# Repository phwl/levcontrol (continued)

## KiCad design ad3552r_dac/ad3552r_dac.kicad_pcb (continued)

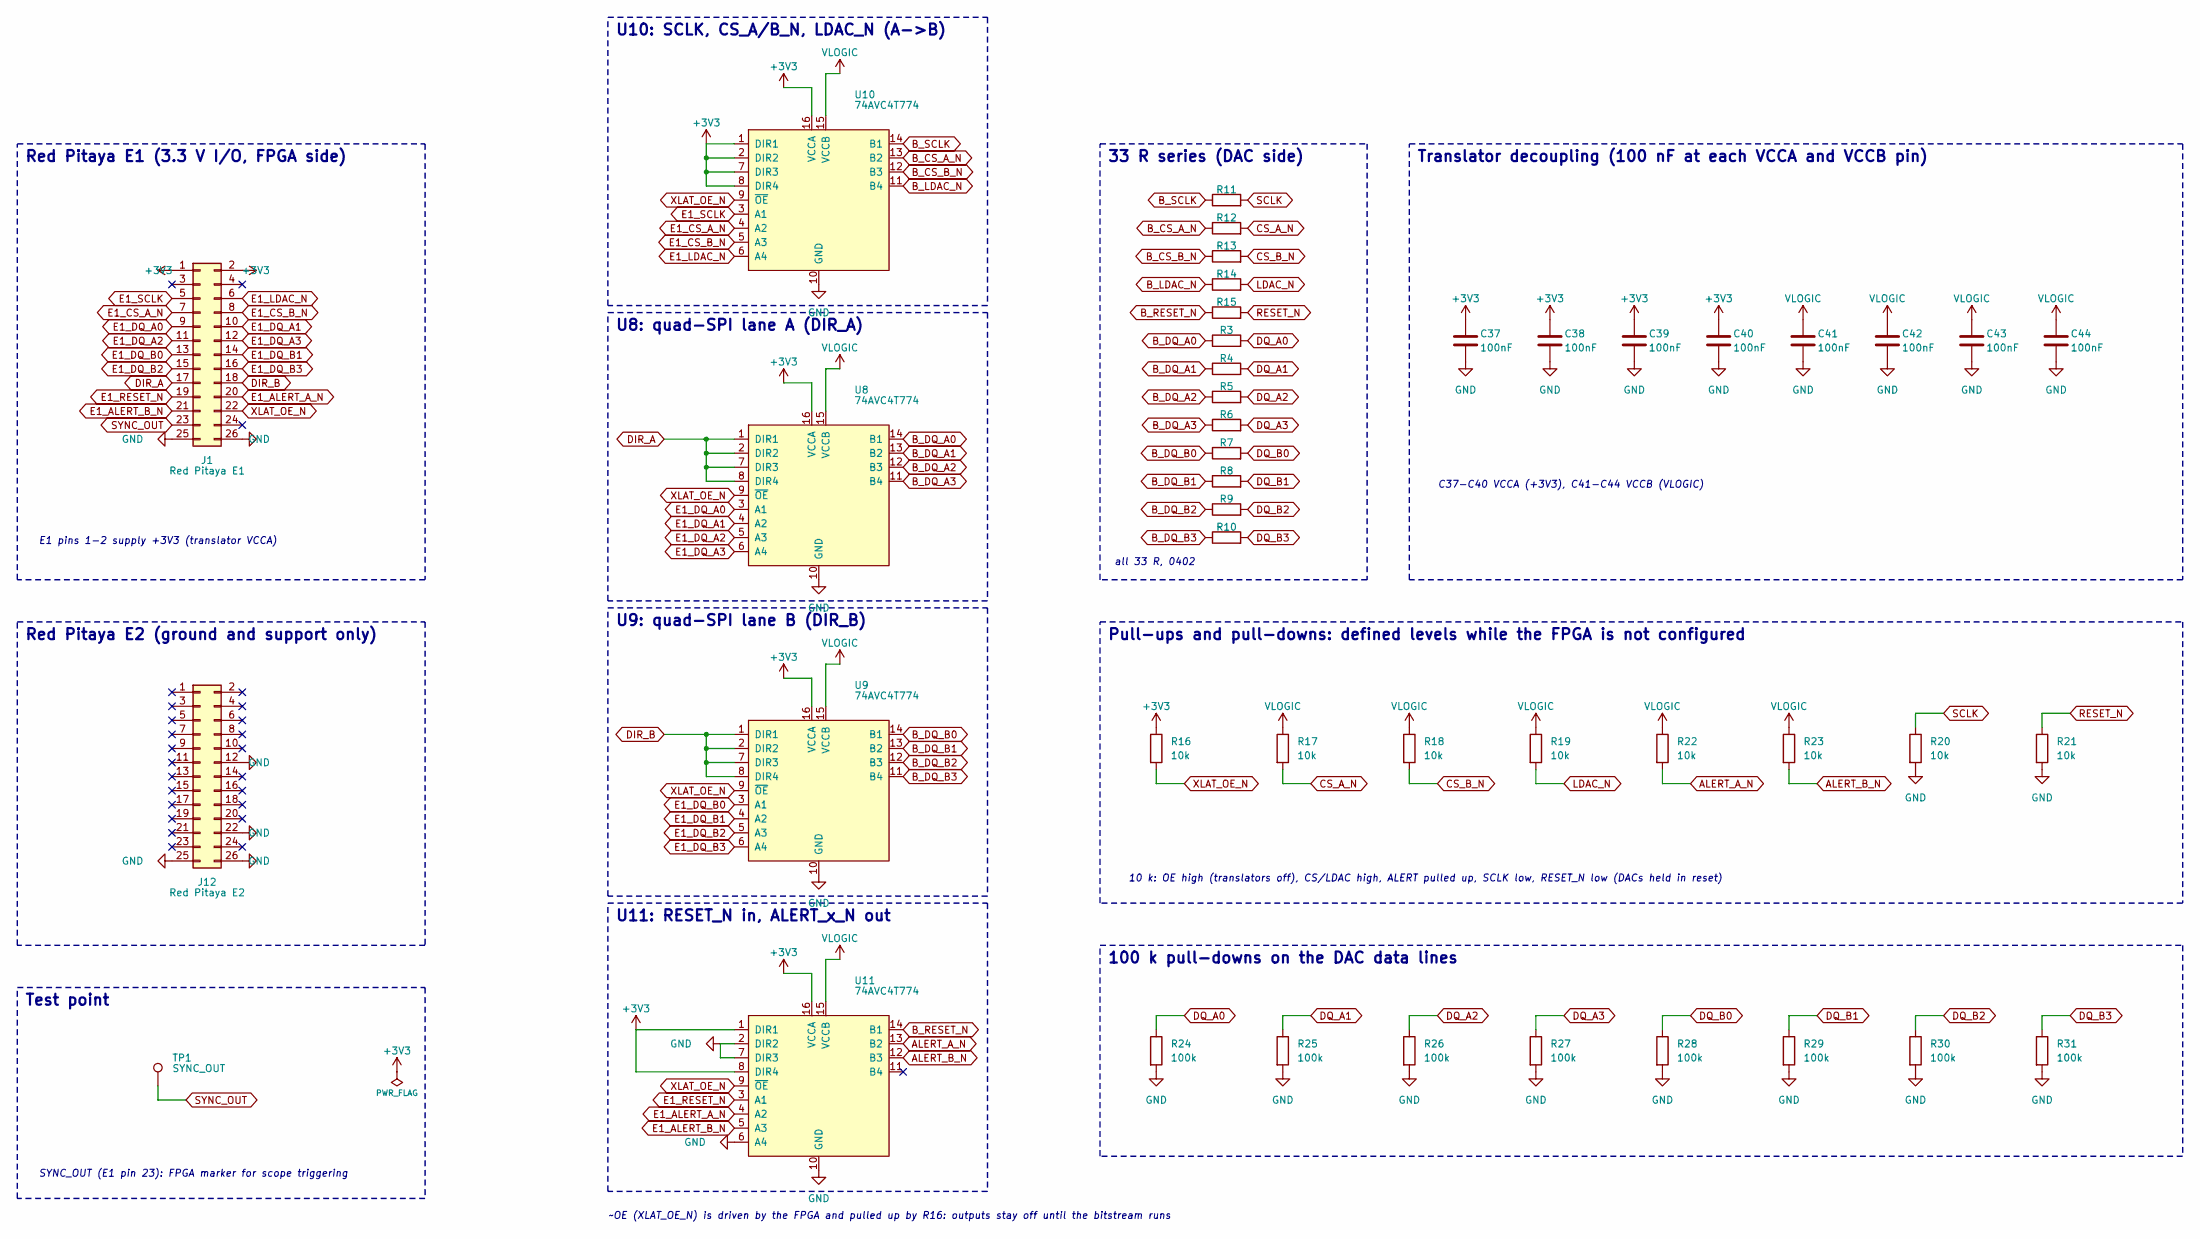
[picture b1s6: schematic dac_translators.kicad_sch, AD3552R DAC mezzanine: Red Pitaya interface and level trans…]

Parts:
C37, C38, C39, C40, C41, C42, C43, C44: 100nF; C_0402_1005Metric; MPN CL05B104KO5NNNC; LCSC C1525
J1: Red Pitaya E1; PinSocket_2x13_P2.54mm_Vertical; MPN ESW-113-33-T-D; LCSC C7498573
J12: Red Pitaya E2; PinSocket_2x13_P2.54mm_Vertical; MPN ESW-113-33-T-D; LCSC C7498573
R3, R4, R5, R6, R7, R8, R9, R10, R11, R12, R13, R14, R15: 33; R_0402_1005Metric; MPN 0402WGF330JTCE; LCSC C25105
R16, R17, R18, R19, R20, R21, R22, R23: 10k; R_0402_1005Metric; MPN 0402WGF1002TCE; LCSC C25744
R24, R25, R26, R27, R28, R29, R30, R31: 100k; R_0402_1005Metric; MPN 0402WGF1003TCE; LCSC C25741
TP1: SYNC_OUT; TestPoint_Pad_D1.5mm
U8, U9, U10, U11: 74AVC4T774; TSSOP-16_4.4x5mm_P0.65mm; MPN 74AVC4T774PWJ; LCSC C546276

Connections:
+3V3: C37.1, C38.1, C39.1, C40.1, J1.1, J1.2, R16.1, U8.16 (VCCA), U9.16 (VCCA), U10.1 (DIR1), U10.2 (DIR2), U10.7 (DIR3), U10.8 (DIR4), U10.16 (VCCA), U11.1 (DIR1), U11.8 (DIR4), U11.16 (VCCA)
ALERT_A_N: R22.2, U11.13 (B2); also elsewhere on the board
ALERT_B_N: R23.2, U11.12 (B3); also elsewhere on the board
B_CS_A_N: R12.1, U10.13 (B2)
B_CS_B_N: R13.1, U10.12 (B3)
B_DQ_A0: R3.1, U8.14 (B1)
B_DQ_A1: R4.1, U8.13 (B2)
B_DQ_A2: R5.1, U8.12 (B3)
B_DQ_A3: R6.1, U8.11 (B4)
B_DQ_B0: R7.1, U9.14 (B1)
B_DQ_B1: R8.1, U9.13 (B2)
B_DQ_B2: R9.1, U9.12 (B3)
B_DQ_B3: R10.1, U9.11 (B4)
B_LDAC_N: R14.1, U10.11 (B4)
B_RESET_N: R15.1, U11.14 (B1)
B_SCLK: R11.1, U10.14 (B1)
CS_A_N: R12.2, R17.2; also elsewhere on the board
CS_B_N: R13.2, R18.2; also elsewhere on the board
DIR_A: J1.17, U8.1 (DIR1), U8.2 (DIR2), U8.7 (DIR3), U8.8 (DIR4)
DIR_B: J1.18, U9.1 (DIR1), U9.2 (DIR2), U9.7 (DIR3), U9.8 (DIR4)
DQ_A0: R3.2, R24.1; also elsewhere on the board
DQ_A1: R4.2, R25.1; also elsewhere on the board
DQ_A2: R5.2, R26.1; also elsewhere on the board
DQ_A3: R6.2, R27.1; also elsewhere on the board
DQ_B0: R7.2, R28.1; also elsewhere on the board
DQ_B1: R8.2, R29.1; also elsewhere on the board
DQ_B2: R9.2, R30.1; also elsewhere on the board
DQ_B3: R10.2, R31.1; also elsewhere on the board
E1_ALERT_A_N: J1.20, U11.4 (A2)
E1_ALERT_B_N: J1.21, U11.5 (A3)
E1_CS_A_N: J1.7, U10.4 (A2)
E1_CS_B_N: J1.8, U10.5 (A3)
E1_DQ_A0: J1.9, U8.3 (A1)
E1_DQ_A1: J1.10, U8.4 (A2)
E1_DQ_A2: J1.11, U8.5 (A3)
E1_DQ_A3: J1.12, U8.6 (A4)
E1_DQ_B0: J1.13, U9.3 (A1)
E1_DQ_B1: J1.14, U9.4 (A2)
E1_DQ_B2: J1.15, U9.5 (A3)
E1_DQ_B3: J1.16, U9.6 (A4)
E1_LDAC_N: J1.6, U10.6 (A4)
E1_RESET_N: J1.19, U11.3 (A1)
E1_SCLK: J1.5, U10.3 (A1)
GND: C37.2, C38.2, C39.2, C40.2, C41.2, C42.2, C43.2, C44.2, J1.25, J1.26, J12.12, J12.22, J12.25, J12.26, R20.2, R21.2, R24.2, R25.2, R26.2, R27.2, R28.2, R29.2, R30.2, R31.2, U8.10 (GND), U9.10 (GND), U10.10 (GND), U11.2 (DIR2), U11.6 (A4), U11.7 (DIR3), U11.10 (GND); also elsewhere on the board
LDAC_N: R14.2, R19.2; also elsewhere on the board
RESET_N: R15.2, R21.1; also elsewhere on the board
SCLK: R11.2, R20.1; also elsewhere on the board
SYNC_OUT: J1.23, TP1.1
VLOGIC: C41.1, C42.1, C43.1, C44.1, R17.1, R18.1, R19.1, R22.1, R23.1, U8.15 (VCCB), U9.15 (VCCB), U10.15 (VCCB), U11.15 (VCCB); also elsewhere on the board
XLAT_OE_N: J1.22, R16.2, U8.9 (~OE), U9.9 (~OE), U10.9 (~OE), U11.9 (~OE)

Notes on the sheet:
U10: SCLK, CS_A/B_N, LDAC_N (A->B)
U8: quad-SPI lane A (DIR_A)
all 33 R, 0402
~OE (XLAT_OE_N) is driven by the FPGA and pulled up by R16: outputs stay off until the bitstream runs
Pull-ups and pull-downs: defined levels while the FPGA is not configured
E1 pins 1-2 supply +3V3 (translator VCCA)
100 k pull-downs on the DAC data lines
10 k: OE high (translators off), CS/LDAC high, ALERT pulled up, SCLK low, RESET_N low (DACs held in reset)
C37-C40 VCCA (+3V3), C41-C44 VCCB (VLOGIC)
Translator decoupling (100 nF at each VCCA and VCCB pin)
Red Pitaya E1 (3.3 V I/O, FPGA side)
Test point
33 R series (DAC side)
U11: RESET_N in, ALERT_x_N out
U9: quad-SPI lane B (DIR_B)
Red Pitaya E2 (ground and support only)
SYNC_OUT (E1 pin 23): FPGA marker for scope triggering

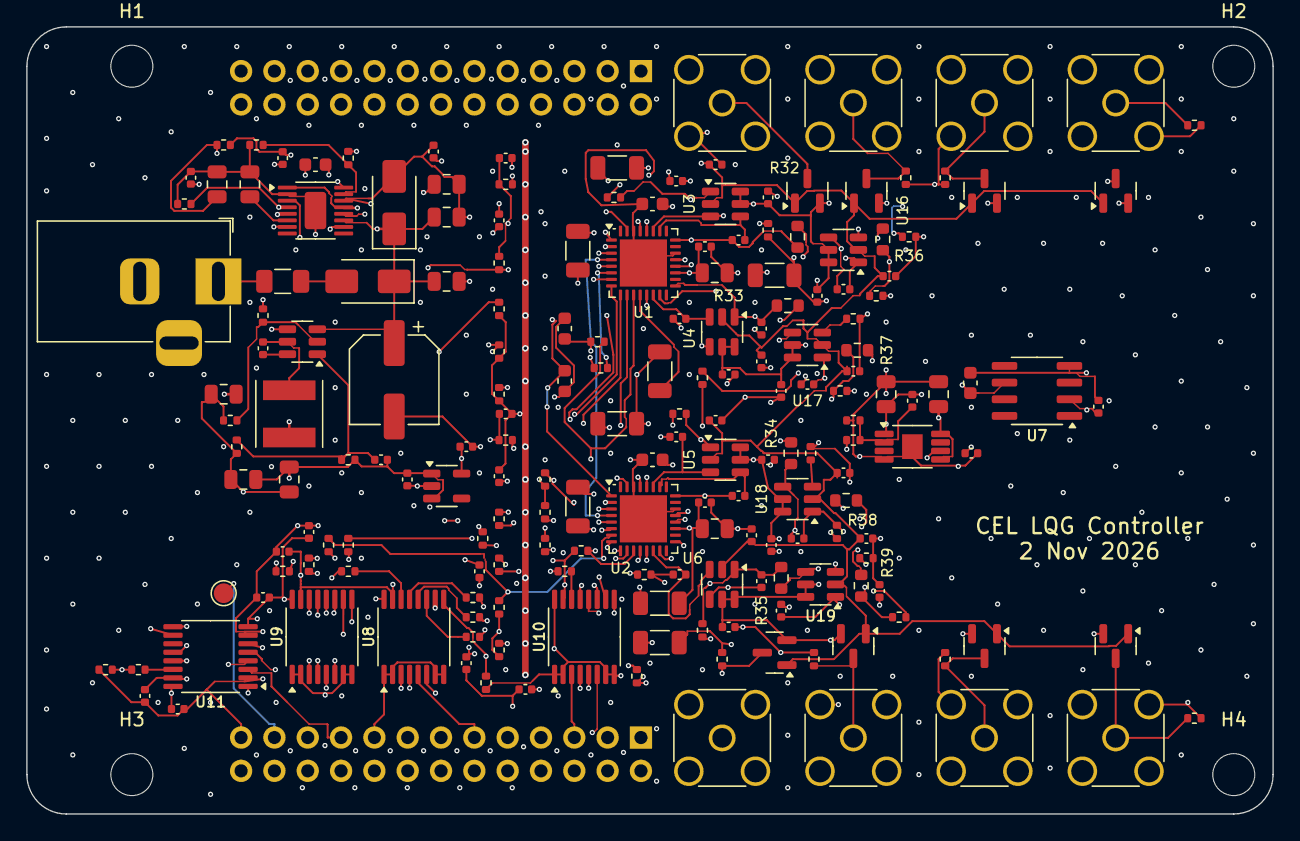
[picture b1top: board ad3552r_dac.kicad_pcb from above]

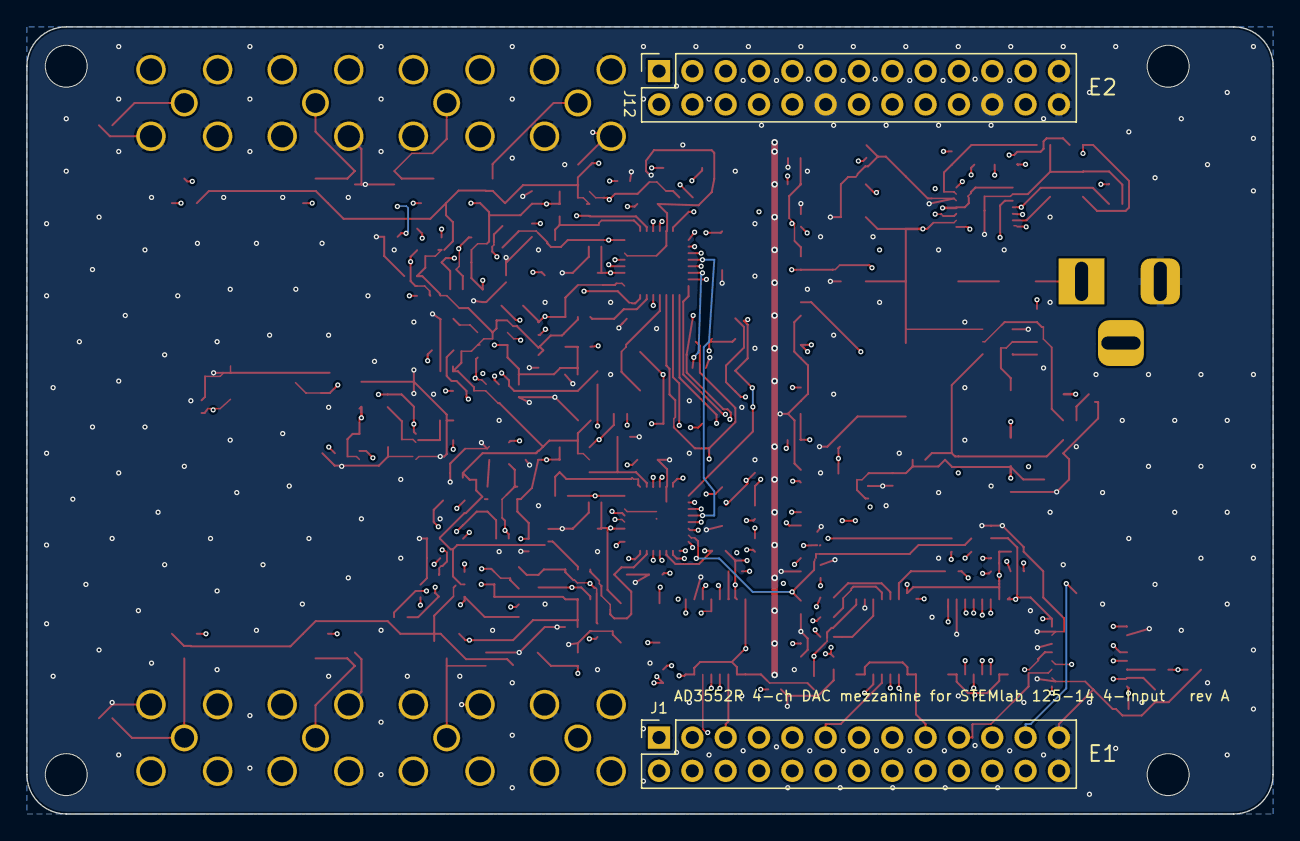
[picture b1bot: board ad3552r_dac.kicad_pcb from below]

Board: 6 copper layers, 95.0 x 60.0 mm, 195 parts (2 on the bottom side), 117 nets.

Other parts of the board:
H1, H2, H3, H4: M3; MountingHole_3.2mm_M3

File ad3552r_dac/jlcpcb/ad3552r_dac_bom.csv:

Comment,Designator,Footprint,LCSC Part #,Manufacturer,MPN,Quantity,Sourcing
1uF,"C1,C2,C3,C4,C76,C77",C_0402_1005Metric,C52923,Samsung,CL05A105KA5NQNC,6,JLCPCB stock
CGA0805X7R106K250MT,"C5,C6,C58,C59,C60,C63,C65,C66,C67,C71",C_0805_2012Metric,C6119932,HRE,CGA0805X7R106K250MT,10,JLCPCB stock
100nF,"C7,C8,C19,C25,C26,C27,C28,C29,C30,C31,C32,C33,C34,C35,C36,C37,C38,C39,C40,C41,C42,C43,C44,C49,C50,C51,C52,C53,C54,C55,C56,C74",C_0402_1005Metric,C1525,Samsung,CL05B104KO5NNNC,32,JLCPCB stock
470nF NP0,"C9,C10,C11,C12,C13,C14,C15,C16",C_1206_3216Metric,C6049896,Murata,GRM31C5C1E474JE01L,8,JLCPCB stock
470nF,"C17,C18",C_0603_1608Metric,C1623,Samsung,CL10B474KA8NNNC,2,JLCPCB stock
4.7uF,C20,C_0603_1608Metric,C19666,Samsung,CL10A475KO8NNNC,1,JLCPCB stock
8.2pF NP0,"C21,C22,C23,C24",C_0402_1005Metric,C1579,FH,0402CG8R2C500NT,4,JLCPCB stock
1pF NP0,"C45,C46,C47,C48",C_0402_1005Metric,C1550,FH,0402CG1R0C500NT,4,JLCPCB stock
47uF,C57,CP_Elec_6.3x5.4,C7469965,FOSAN,FVH025ADA470M0654,1,JLCPCB stock
10nF,"C61,C62,C68,C69",C_0402_1005Metric,C15195,Samsung,CL05B103KB5NNNC,4,JLCPCB stock
1uF 25V X7R,C64,C_0603_1608Metric,C106858,YAGEO,CC0603KRX7R8BB105,1,JLCPCB stock
10pF,C70,C_0402_1005Metric,C1545,FH,0402CG100J500NT,1,JLCPCB stock
22uF,"C72,C73",C_0805_2012Metric,C45783,Samsung,CL21A226MAQNNNE,2,JLCPCB stock
100pF,C75,C_0402_1005Metric,C1546,FH,0402CG101J500NT,1,JLCPCB stock
BAV99,"D1,D2,D3,D4,D5,D6,D7,D8",SOT-23,C2500,Nexperia,"BAV99,215",8,JLCPCB stock
40V 2A,D9,D_SMA,C50645,MDD,SS24,1,JLCPCB stock
SMAJ15A,D10,D_SMA,C86819,Brightking,SMAJ15A/TR13,1,JLCPCB stock
0.5A hold,F1,Fuse_1206_3216Metric,C492011,Polytronics (PTTC),SMD1206P050TF/24,1,JLCPCB stock
BLM18PG221SN1D,"FB1,FB2",L_0603_1608Metric,C80165,Murata,BLM18PG221SN1D,2,JLCPCB stock
ESW-113-33-T-D,"J1,J12",PinSocket_2x13_P2.54mm_Vertical,C7498573,Samtec,ESW-113-33-T-D,2,"Global Sourcing, through-hole"
+12V IN,J2,BarrelJack_Horizontal,C3096093,CUI Devices,PJ-102AH,1,"JLCPCB stock, through-hole"
132134,"J4,J5,J6,J7,J8,J9,J10,J11",SMA_Amphenol_132134_Vertical,C3174425,Amphenol,132134,8,"JLCPCB stock, through-hole"
3.3uH,L1,L_Taiyo-Yuden_NR-50xx,C305173,Sunlord,SWPA5040S3R3NT,1,JLCPCB stock
1k,"R1,R2",R_0402_1005Metric,C11702,UNI-ROYAL,0402WGF1001TCE,2,JLCPCB stock
33,"R3,R4,R5,R6,R7,R8,R9,R10,R11,R12,R13,R14,R15",R_0402_1005Metric,C25105,UNI-ROYAL,0402WGF330JTCE,13,JLCPCB stock
10k,"R16,R17,R18,R19,R20,R21,R22,R23",R_0402_1005Metric,C25744,UNI-ROYAL,0402WGF1002TCE,8,JLCPCB stock
100k,"R24,R25,R26,R27,R28,R29,R30,R31,R61,R63,R65,R68",R_0402_1005Metric,C25741,UNI-ROYAL,0402WGF1003TCE,12,JLCPCB stock
2.49k 0.1%,"R32,R33,R34,R35,R36,R37,R38,R39",R_0603_1608Metric,C861299,YAGEO,RT0603BRD072K49L,8,JLCPCB stock
1.24k,"R40,R41,R42,R43",R_0402_1005Metric,C25864,UNI-ROYAL,0402WGF1241TCE,4,JLCPCB stock
49.9,"R44,R45,R46,R47,R48,R49,R50,R51",R_0402_1005Metric,C25120,UNI-ROYAL,0402WGF499JTCE,8,JLCPCB stock
1M,"R52,R53,R54,R55,R56,R57,R58,R59",R_0402_1005Metric,C26083,UNI-ROYAL,0402WGF1004TCE,8,JLCPCB stock
324k,R60,R_0402_1005Metric,C113480,UNI-ROYAL,0402WGF3243TCE,1,JLCPCB stock
316k,"R62,R64",R_0402_1005Metric,C25777,UNI-ROYAL,0402WGF3163TCE,2,JLCPCB stock
130k,R66,R_0402_1005Metric,C52929,UNI-ROYAL,0402WGF1303TCE,1,JLCPCB stock
62k,R67,R_0402_1005Metric,C37825,UNI-ROYAL,0402WGF6202TCE,1,JLCPCB stock
36k,R69,R_0402_1005Metric,C43676,UNI-ROYAL,0402WGF3602TCE,1,JLCPCB stock
AD3552R,"U1,U2",LFCSP-32-1EP_5x5mm_P0.5mm_EP3.6x3.6mm_AD3552R,C4748801,Analog Devices,AD3552RBCPZ16,2,Global Sourcing
ADA4807-1,"U3,U4,U5,U6,U16,U17,U18,U19",SOT-23-6,C2058411,Analog Devices,ADA4807-1ARJZ-R7,8,Global Sourcing
ADR4525BRZ,U7,SOIC-8_3.9x4.9mm_P1.27mm,C403914,Analog Devices,ADR4525BRZ-R7,1,JLCPCB stock
74AVC4T774,"U8,U9,U10,U11",TSSOP-16_4.4x5mm_P0.65mm,C546276,Nexperia,74AVC4T774PWJ,4,JLCPCB stock
TPS7A4901,U12,HVSSOP-8-1EP_3x3mm_P0.65mm_EP1.57x1.89mm,C16430,Texas Instruments,TPS7A4901DGNR,1,JLCPCB stock
LTC3260,U13,MSOP-16-1EP_3x4mm_P0.5mm_EP1.65x2.85mm,C684387,Analog Devices,LTC3260EMSE#TRPBF,1,JLCPCB stock
AP63201,U14,TSOT-23-6,C2071044,Diodes Incorporated,AP63201WU-7,1,JLCPCB stock
TLV75518P,U15,SOT-23-5,C2877863,Texas Instruments,TLV75518PDBVR,1,JLCPCB stock

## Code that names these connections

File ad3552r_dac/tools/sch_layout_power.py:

#!/usr/bin/env python3
"""Layout of the 'Power' sheet: 12 V input, AVDD LDO, +/-5 V charge pump, +2.5 V buck, +1.8 V LDO and the DVDD/VLOGIC beads."""
import sys
sys.path.insert(0, 'tools')
from schgen import Sheet

sh = Sheet('dac_power.kicad_sch', paper='A3', title='AD3552R DAC mezzanine: power supplies',
           comment=('+12 V in -> AVDD 5.02 V, +/-5 V, +2.5 V, +1.8 V (DVDD, VLOGIC)', 'LQG Controller, CEL'))

def above(x, y_top):
    """IC reference and value stacked above the body (body top edge at y_top)"""
    return {'Reference': (x, y_top - 3.81, None), 'Value': (x, y_top - 1.905, None)}

# ---------------------------------------------------------------- 12 V input and protection
Y = 50.8
sh.box(17.78, 27.94, 129.54, 72.39, '+12 V input and protection')
sh.place('J2', 25.4, Y + 2.54, fields={'Reference': (22.86, Y - 5.08, None), 'Value': (22.86, Y - 3.175, None)})
sh.place('F1', 45.72, Y, rot=90)
sh.place('D9', 60.96, Y, rot=180)
sh.place('D10', 74.93, Y + 3.81, rot=270)
sh.place('C57', 87.63, Y + 3.81)
sh.place('C58', 100.33, Y + 3.81)
sh.wire('J2.1', 'F1.1'); sh.wire('F1.2', 'D9.2')
sh.wire('D9.1', (118.11, Y))
sh.label('+12V', (118.11, Y), 90); sh.flag((109.22, Y))
sh.wire('J2.2', (35.56, Y + 5.08)); sh.label('GND', (35.56, Y + 5.08), 270)
sh.text('0.5 A polyfuse, Schottky reverse-polarity diode, 15 V TVS, 47 uF bulk', 22.86, Y + 13.97, size=1.27, italic=True)

# ---------------------------------------------------------------- AVDD LDO
x, y = 182.88, 50.8
sh.box(137.16, 27.94, 285.75, 76.2, 'AVDD 5.02 V: low-noise LDO (TPS7A4901)')
sh.place('U12', x, y, fields=above(x, y - 5.08))
sh.place('C59', x - 35.56, y + 1.27)
sh.wire('U12.8', (x - 35.56, y - 2.54)); sh.label('+12V', (x - 35.56, y - 2.54), 90)
sh.wire('U12.5', (x - 22.86, y), (x - 22.86, y - 2.54))                 # EN tied to IN
sh.place('C61', x - 20.32, y + 6.35, fields='left')
sh.wire('U12.6', (x - 20.32, y + 2.54))                                  # NR/SS soft-start cap
sh.wire('U12.9', (x - 1.27, y + 10.16), (x - 3.81, y + 10.16))
sh.wire('U12.4', (x - 3.81, y + 10.16)); sh.label('GND', (x - 3.81, y + 10.16), 270)
sh.place('R60', x + 25.4, y + 1.27)
sh.place('R61', x + 25.4, y + 8.89)
sh.place('C62', x + 35.56, y + 1.27)
sh.place('C60', x + 48.26, y + 1.27)
sh.wire('U12.1', (x + 60.96, y - 2.54)); sh.label('AVDD', (x + 60.96, y - 2.54), 90)
sh.wire('U12.2', (x + 20.32, y), (x + 20.32, y + 5.08), 'R60.2')
sh.wire('C62.2', (x + 35.56, y + 5.08), (x + 25.4, y + 5.08))
sh.text('AVDD = V_FB (1 + R60/R61); C62 feed-forward; C61 soft start / noise filter', x - 38.1, y + 20.32, size=1.27, italic=True)

# ---------------------------------------------------------------- +/-5 V charge pump
x, y = 68.58, 121.92
sh.box(17.78, 86.36, 285.75, 154.94, '+/-5 V: inverting charge pump with positive and negative LDOs (LTC3260)')
sh.place('U13', x, y, fields={'Reference': (x - 15.24, y + 17.78, None), 'Value': (x - 15.24, y + 19.685, None)})
sh.place('C64', x, y - 20.32, rot=90)
sh.wire('U13.10', (x - 1.27, y - 15.24), (x - 3.81, y - 15.24), 'C64.1')
sh.wire('U13.7', (x + 1.27, y - 15.24), (x + 3.81, y - 15.24), 'C64.2')
sh.wire('U13.11', (x - 25.4, y - 7.62)); sh.label('+12V', (x - 25.4, y - 7.62), 90)
sh.wire('U13.1', (x - 30.48, y - 5.08)); sh.label('+2V5', (x - 30.48, y - 5.08), 90)
sh.wire('U13.13', (x - 20.32, y - 2.54), (x - 20.32, y - 5.08))
sh.wire('U13.14', (x - 20.32, y), (x - 20.32, y + 5.08)); sh.wire('U13.2', (x - 20.32, y + 2.54))
sh.label('GND', (x - 20.32, y + 5.08), 270)
sh.text('EN+/EN- from +2V5: the pump starts after the buck', x - 48.26, y + 24.13, size=1.27, italic=True)
for pin in ('6', '12', '15', '16', '5', '4', '3'):                     # right-hand pins: a stub, then the net tag
    p = sh.pin('U13.' + pin)
    xe = x + (33.02 if pin in ('12', '5') else 22.86)                  # rails a little further out than the labels
    sh.wire(p, (xe, p[1])); sh.label(sh.pin_net[('U13', pin)], (xe, p[1]), 0)
# output networks, each a small wired group tagged with the pin's net
X = x + 50.8
sh.place('C65', X, y - 12.7); sh.tag_off('C65.1', dh=-5.08)
sh.place('C63', X + 12.7, y - 12.7)
sh.place('C66', X + 25.4, y - 12.7)
sh.place('C67', X + 35.56, y - 12.7)
sh.place('C68', X + 48.26, y - 12.7); sh.tag_off('C68.1', dh=5.08)
sh.place('C69', X + 63.5, y - 12.7); sh.tag_off('C69.1', dh=5.08)
# positive LDO divider: +5V - R62 - ADJP - R63 - GND
sh.place('R62', X + 7.62, y + 7.62); sh.place('R63', X + 7.62, y + 17.78)
sh.wire('R62.2', 'R63.1'); sh.wire((X + 7.62, y + 12.7), (X + 15.24, y + 12.7)); sh.label('/Power/ADJP', (X + 15.24, y + 12.7), 0)
sh.text('+5 V = 1.2 V (1 + R62/R63)', X, y + 29.21, size=1.27, italic=True)
# negative LDO divider: -5V - R64 (|| C70) - ADJN - R65 - GND
sh.place('R64', X + 48.26, y + 7.62); sh.place('R65', X + 48.26, y + 17.78)
sh.place('C70', X + 58.42, y + 7.62)
sh.wire('R64.2', 'R65.1'); sh.wire('C70.2', (X + 58.42, y + 12.7), (X + 48.26, y + 12.7))
sh.wire('R64.1', (X + 48.26, y + 2.54), (X + 58.42, y + 2.54), 'C70.1')
sh.wire((X + 58.42, y + 12.7), (X + 66.04, y + 12.7)); sh.label('/Power/ADJN', (X + 66.04, y + 12.7), 0)
sh.label('-5V', (X + 53.34, y + 2.54), 90)
sh.text('-5 V = -1.2 V (1 + R64/R65); C70 feed-forward', X + 40.64, y + 29.21, size=1.27, italic=True)

# ---------------------------------------------------------------- +2.5 V buck
x, y = 66.04, 203.2
sh.box(17.78, 170.18, 158.75, 237.49, '+2.5 V: buck converter (AP63201), enabled once AVDD is up')
sh.place('U14', x, y, fields=above(x, y - 5.08))
sh.wire('U14.3', (x - 12.7, y - 2.54), (x - 12.7, y - 15.24), (x - 43.18, y - 15.24))
sh.label('+12V', (x - 43.18, y - 15.24), 90)
sh.place('C71', x - 35.56, y - 11.43, fields='left')
sh.place('R68', x - 25.4, y - 1.27, fields='left'); sh.place('R69', x - 25.4, y + 6.35, fields='left')
sh.label('AVDD', 'R68.1', 90)
sh.wire('U14.2', 'R68.2'); sh.label('/Power/BUCK_EN', (x - 22.86, y + 2.54), 0)
sh.place('L1', x + 30.48, y - 2.54, rot=90)
sh.wire('U14.5', 'L1.1'); sh.label('/Power/BUCK_SW', (x + 17.78, y - 2.54), 0)
sh.place('C74', x + 15.24, y - 6.35, rot=180, fields='left')
sh.tag_off('C74.2', '/Power/BUCK_BST', dv=-2.54, dh=5.08)
sh.place('R66', x + 43.18, y + 1.27); sh.place('R67', x + 43.18, y + 8.89)
sh.place('C75', x + 53.34, y + 1.27)
sh.place('C72', x + 63.5, y + 1.27); sh.place('C73', x + 73.66, y + 1.27)
sh.wire('L1.2', (x + 85.09, y - 2.54)); sh.label('+2V5', (x + 85.09, y - 2.54), 90); sh.flag((x + 58.42, y - 2.54))
sh.wire('U14.1', (x + 38.1, y + 2.54), (x + 38.1, y + 5.08), 'R66.2')
sh.wire('C75.2', (x + 53.34, y + 5.08), (x + 43.18, y + 5.08))
sh.label('/Power/BUCK_FB', (x + 22.86, y + 2.54), 0)
sh.text('EN = AVDD x R69/(R68+R69): starts after AVDD;  +2.5 V = 0.8 V (1 + R66/R67)', x - 45.72, y + 24.13, size=1.27, italic=True)

# ---------------------------------------------------------------- +1.8 V LDO and the DAC logic rails
x, y = 195.58, 203.2
sh.box(166.37, 170.18, 285.75, 237.49, '+1.8 V LDO (TLV75518P) -> DVDD and VLOGIC')
sh.place('U15', x, y, fields=above(x, y - 5.08))
sh.place('C76', x - 15.24, y + 1.27)
sh.wire('U15.1', (x - 22.86, y - 2.54)); sh.label('+2V5', (x - 22.86, y - 2.54), 90)
sh.wire('U15.3', (x - 10.16, y), (x - 10.16, y - 2.54))
sh.place('C77', x + 12.7, y + 1.27)
sh.place('FB1', x + 35.56, y - 2.54, rot=90)
sh.place('FB2', x + 35.56, y + 12.7, rot=90)
sh.wire('U15.5', 'FB1.1'); sh.label('+1V8', (x + 20.32, y - 2.54), 90)
sh.wire((x + 25.4, y - 2.54), (x + 25.4, y + 12.7), 'FB2.1')
sh.wire('FB1.2', (x + 53.34, y - 2.54)); sh.label('DVDD', (x + 53.34, y - 2.54), 90)
sh.wire('FB2.2', (x + 53.34, y + 12.7)); sh.label('VLOGIC', (x + 53.34, y + 12.7), 90)
sh.text('Separate beads keep the DAC digital current off the logic supply', x - 25.4, y + 24.13, size=1.27, italic=True)

# ---------------------------------------------------------------- notes
N = 297.18
sh.box(N - 2.54, 27.94, 406.4, 101.6, 'Rails and start-up')
for i, s in enumerate([
        '+12V   external, about 145 mA total (1.7 W)',
        'AVDD   5.02 V, DAC analog supply and ADR4525 input',
        '+5V    LTC3260 LDO+, amplifier positive rail',
        '-5V    LTC3260 LDO-, amplifier negative rail',
        '+2V5   AP63201 buck: feeds the 1.8 V LDO, enables U13',
        '+1V8   TLV75518P -> DVDD (FB1) and VLOGIC (FB2)',
        '+3V3   from the Red Pitaya E1 header (VCCA)',
        '',
        'Start-up order (the AD3552R wants AVDD first):',
        '  1. +12 V on: U12 brings up AVDD',
        '  2. AVDD above about 1.4 V enables U14: +2V5',
        '  3. +2V5 enables U15 (+1V8) and U13 (+/-5 V)',
        '  4. RESET_N held low by R21 until the FPGA releases it',
]):
    sh.text(s, N, 35.56 + i * 4.445, size=1.524)
print(sh.write())

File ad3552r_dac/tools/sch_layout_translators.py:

#!/usr/bin/env python3
"""Layout of the 'E1 translators' sheet: Red Pitaya E1/E2 headers, four 74AVC4T774 level translators (3.3 V <-> 1.8 V),
33 ohm series resistors, pull-ups / pull-downs and the translator decoupling."""
import sys
sys.path.insert(0, 'tools')
from schgen import Sheet

sh = Sheet('dac_translators.kicad_sch', paper='A3', title='AD3552R DAC mezzanine: Red Pitaya interface and level translators',
           comment=('E1 3.3 V (VCCA) <-> DAC 1.8 V (VCCB = VLOGIC); 33 R series at the DAC side', 'LQG Controller, CEL'))

# ---------------------------------------------------------------- headers
x, y = 48.26, 76.2
sh.box(15.24, 38.1, 88.9, 116.84, 'Red Pitaya E1 (3.3 V I/O, FPGA side)')
sh.place('J1', x, y, fields={'Reference': (x + 1.27, y + 19.05, None), 'Value': (x + 1.27, y + 20.955, None)})
sh.text('E1 pins 1-2 supply +3V3 (translator VCCA)', 19.05, 109.22, size=1.27, italic=True)
x, y = 48.26, 152.4
sh.box(15.24, 124.46, 88.9, 182.88, 'Red Pitaya E2 (ground and support only)')
sh.place('J12', x, y, fields={'Reference': (x + 1.27, y + 19.05, None), 'Value': (x + 1.27, y + 20.955, None)})

# ---------------------------------------------------------------- translators
def xlat(ref, x, y, title, dir_mode):
    sh.box(x - 38.1, y - 33.02, x + 30.48, y + 19.05, title)
    sh.place(ref, x, y, fields={'Reference': (x + 6.35, y - 19.05, 'left'), 'Value': (x + 6.35, y - 17.145, 'left')})
    sh.wire('%s.16' % ref, (x - 1.27, y - 20.32), (x - 6.35, y - 20.32)); sh.label('+3V3', (x - 6.35, y - 20.32), 90)
    sh.wire('%s.15' % ref, (x + 1.27, y - 22.86), (x + 3.81, y - 22.86)); sh.label('VLOGIC', (x + 3.81, y - 22.86), 90)
    d = {k: sh.pin('%s.%s' % (ref, k)) for k in ('1', '2', '7', '8')}     # DIR1, DIR2, DIR3, DIR4 (top to bottom)
    if dir_mode in ('DIR_A', 'DIR_B', '+3V3'):        # all four direction pins together
        for k in d:
            sh.wire(d[k], (x - 20.32, d[k][1]))
        sh.wire((x - 20.32, d['1'][1]), (x - 20.32, d['8'][1]))
        if dir_mode == '+3V3':
            sh.label('+3V3', (x - 20.32, d['1'][1]), 90)
        else:
            sh.wire((x - 20.32, d['1'][1]), (x - 27.94, d['1'][1])); sh.label(dir_mode, (x - 27.94, d['1'][1]), 180)
    else:                                              # U11: DIR1/DIR4 high (A->B), DIR2/DIR3 low (B->A, the ALERTs)
        sh.wire(d['2'], (x - 17.78, d['2'][1]), (x - 17.78, d['7'][1]), d['7'])
        sh.label('GND', (x - 17.78, d['2'][1]), 180)
        sh.wire(d['1'], (x - 33.02, d['1'][1]), (x - 33.02, d['8'][1]), d['8'])
        sh.label('+3V3', (x - 33.02, d['1'][1]), 90)

X = 160.02
xlat('U10', X, 48.26, 'U10: SCLK, CS_A/B_N, LDAC_N (A->B)', '+3V3')
xlat('U8', X, 101.6, 'U8: quad-SPI lane A (DIR_A)', 'DIR_A')
xlat('U9', X, 154.94, 'U9: quad-SPI lane B (DIR_B)', 'DIR_B')
xlat('U11', X, 208.28, 'U11: RESET_N in, ALERT_x_N out', 'mixed')
sh.text('~OE (XLAT_OE_N) is driven by the FPGA and pulled up by R16: outputs stay off until the bitstream runs', 121.92, 231.14, size=1.27, italic=True)

# ---------------------------------------------------------------- series resistors
X = 233.68
sh.box(X - 22.86, 38.1, X + 25.4, 116.84, '33 R series (DAC side)')
for i, r in enumerate(['R11', 'R12', 'R13', 'R14', 'R15', 'R3', 'R4', 'R5', 'R6', 'R7', 'R8', 'R9', 'R10']):
    sh.place(r, X, 48.26 + i * 5.08, rot=90, fields={'Reference': (X, 48.26 + i * 5.08 - 1.905, None), 'Value': None})
sh.text('all 33 R, 0402', X - 20.32, 113.03, size=1.27, italic=True)

# ---------------------------------------------------------------- pull resistors
def pull(r, x, y):
    n1 = sh.pin_net[(r, '1')]; n2 = sh.pin_net[(r, '2')]
    sh.place(r, x, y)
    if n2 in ('GND',):                     # pull-down: the signal on top
        sh.tag_off(r + '.1', dv=-2.54, dh=5.08)
    else:                                  # pull-up: the rail on top, the signal below
        sh.tag_off(r + '.2', dv=2.54, dh=5.08)

Y = 147.32
sh.box(210.82, 124.46, 406.4, 175.26, 'Pull-ups and pull-downs: defined levels while the FPGA is not configured')
for i, r in enumerate(['R16', 'R17', 'R18', 'R19', 'R22', 'R23', 'R20', 'R21']):
    pull(r, 220.98 + i * 22.86, Y)
sh.text('10 k: OE high (translators off), CS/LDAC high, ALERT pulled up, SCLK low, RESET_N low (DACs held in reset)', 215.9, 170.18, size=1.27, italic=True)
Y = 201.93
sh.box(210.82, 182.88, 406.4, 220.98, '100 k pull-downs on the DAC data lines')
for i, r in enumerate(['R24', 'R25', 'R26', 'R27', 'R28', 'R29', 'R30', 'R31']):
    pull(r, 220.98 + i * 22.86, Y)

# ---------------------------------------------------------------- decoupling, test point
Y = 73.66
sh.box(266.7, 38.1, 406.4, 116.84, 'Translator decoupling (100 nF at each VCCA and VCCB pin)')
for i, c in enumerate(['C37', 'C38', 'C39', 'C40', 'C41', 'C42', 'C43', 'C44']):
    sh.place(c, 276.86 + i * 15.24, Y)
sh.text('C37-C40 VCCA (+3V3), C41-C44 VCCB (VLOGIC)', 271.78, 99.06, size=1.27, italic=True)
sh.box(15.24, 190.5, 88.9, 228.6, 'Test point')
sh.place('TP1', 40.64, 208.28, fields={'Reference': (43.18, 203.2, 'left'), 'Value': (43.18, 205.105, 'left')})
sh.tag_off('TP1.1', dv=2.54, dh=5.08)
sh.text('SYNC_OUT (E1 pin 23): FPGA marker for scope triggering', 19.05, 223.52, size=1.27, italic=True)
sh.flag((83.82, 205.74), '+3V3')
print(sh.write())
